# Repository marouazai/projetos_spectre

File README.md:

# projetos_spectre

1. Objectif du programme

Le programme réalise un analyseur de spectre audio temps réel sur la carte STM32F746G-DISCO.

Son rôle est de :

Capturer le son provenant du jack audio 3.5 mm.
Numériser ce son à 44,1 kHz.
Calculer sa Transformée de Fourier Rapide (FFT).
Afficher simultanément :
la forme d'onde du signal (oscilloscope)
le spectre fréquentiel (barres FFT colorées).

3. Logique générale du système

Le programme suit la chaîne de traitement suivante :

Signal Audio >>>Codec WM8994 >>> SAI2 >>> DMA >>> Buffer Audio >>> Prétraitement >>> FFT >>> Calcul des amplitudes>>> Affichage LCD

Le principe est :
  
1.Le matériel récupère le son.
2.Le DMA stocke les échantillons sans utiliser le CPU.
3.Le processeur analyse les données reçues.
4.Les résultats sont affichés en temps réel.

3. Taille de la FFT

Le programme utilise une FFT de 1024 points. À chaque traitement, un bloc de 1024 échantillons est analysé pour extraire son contenu fréquentiel. Ce choix représente un compromis entre la précision fréquentielle et la rapidité d'exécution. Avec une fréquence d'échantillonnage de 44,1 kHz, la résolution fréquentielle obtenue est d'environ 43 Hz par bin, ce qui permet de distinguer correctement les différentes composantes du signal audio.

4.Utilisation du DMA

Le transfert des données audio vers la mémoire est assuré par le contrôleur DMA (Direct Memory Access). Cette technique permet de transférer les échantillons directement depuis le périphérique audio vers la mémoire RAM sans solliciter le processeur. Ainsi, le microcontrôleur reste disponible pour effectuer les calculs FFT et l'affichage graphique, ce qui améliore considérablement les performances du système en temps réel.

5.Technique du Double Buffering

Afin d'éviter toute perte de données pendant l'acquisition audio, le programme utilise une technique appelée double buffering. Le buffer mémoire est divisé en deux parties. Pendant que le DMA remplit une moitié du buffer avec de nouvelles données audio, le processeur traite simultanément l'autre moitié. Cette méthode garantit une acquisition continue du signal tout en permettant son traitement en temps réel.

6.Gestion des interruptions DMA

Le DMA génère des interruptions lorsque la moitié ou la totalité du buffer est remplie. Ces interruptions ne réalisent aucun traitement complexe ; elles se contentent de positionner des indicateurs appelés flags. Cette approche permet de maintenir des interruptions très courtes et de réserver les calculs lourds, tels que la FFT et l'affichage graphique, à la boucle principale du programme. Cette organisation constitue une bonne pratique dans les systèmes embarqués temps réel.

7.Initialisation du système d'affichage

Lors du démarrage du programme, le module d'affichage LCD est initialisé afin de préparer l'écran pour l'affichage graphique. Le système configure les couleurs, les polices ainsi que les différentes zones d'affichage. Une zone supérieure est réservée à la représentation temporelle du signal tandis qu'une zone inférieure est utilisée pour afficher le spectre fréquentiel obtenu après calcul de la FFT.

8.Application de la fenêtre de Hanning

Avant d'effectuer la FFT, le programme applique une fenêtre de Hanning aux échantillons audio. Cette opération consiste à multiplier chaque échantillon par un coefficient calculé selon une fonction mathématique spécifique. L'objectif est de réduire les effets de bord liés à la découpe du signal en blocs, ce qui diminue les fuites spectrales et améliore la précision de l'analyse fréquentielle.

9.Calcul de la Transformée de Fourier Rapide

La FFT est réalisée grâce à la bibliothèque CMSIS-DSP optimisée pour les processeurs ARM Cortex-M7. Cette opération transforme le signal du domaine temporel vers le domaine fréquentiel. Le résultat permet de déterminer quelles fréquences sont présentes dans le signal ainsi que leur amplitude respective. Cette étape constitue le cœur du fonctionnement de l'analyseur de spectre.

10.Calcul des amplitudes fréquentielles

Après le calcul de la FFT, le programme détermine l'amplitude de chaque composante fréquentielle. Pour cela, il calcule le module des valeurs complexes obtenues à la sortie de la FFT. Ces amplitudes représentent l'énergie contenue dans chaque fréquence du signal audio et servent ensuite à construire l'affichage du spectre.

11.Conversion en décibels

Les amplitudes calculées sont converties en décibels à l'aide de la formule logarithmique 20·log10(x). Cette conversion permet d'obtenir une représentation plus proche de la perception humaine du son.

12.Affichage du spectre fréquentiel

La partie inférieure de l'écran affiche le spectre audio sous forme de 60 barres verticales. La hauteur de chaque barre est proportionnelle à l'amplitude de la bande fréquentielle correspondante. Les couleurs évoluent progressivement du vert vers le rouge, permettant d'identifier visuellement les différentes zones du spectre, des basses fréquences aux hautes fréquences.

13.Lissage de l'affichage

Afin d'améliorer le confort visuel, le programme applique un algorithme de lissage aux hauteurs des barres du spectre. Les barres montent rapidement lorsqu'une fréquence apparaît mais redescendent plus lentement lorsqu'elle disparaît.

14.Boucle principale du programme

La boucle principale assure la surveillance continue des indicateurs générés par le DMA. Lorsqu'une moitié du buffer est disponible, les données correspondantes sont immédiatement traitées par le module FFT puis affichées à l'écran. Grâce au double buffering, cette opération peut être réalisée en continu sans interrompre l'acquisition audio. Le système fonctionne ainsi en temps réel avec une faible charge processeur et sans perte d'échantillons.

Conclusion

L'architecture du programme repose sur une combinaison efficace entre acquisition audio, traitement numérique du signal et affichage graphique. L'utilisation du DMA, du double buffering et de la bibliothèque CMSIS-DSP permet de réaliser une analyse fréquentielle en temps réel tout en garantissant des performances élevées sur le microcontrôleur STM32F746G-DISCO. Le système offre ainsi une visualisation claire et instantanée des caractéristiques temporelles et fréquentielles du signal audio.

Réalisées par : Maroua Zaid , Chaimaa Es-saoudi .

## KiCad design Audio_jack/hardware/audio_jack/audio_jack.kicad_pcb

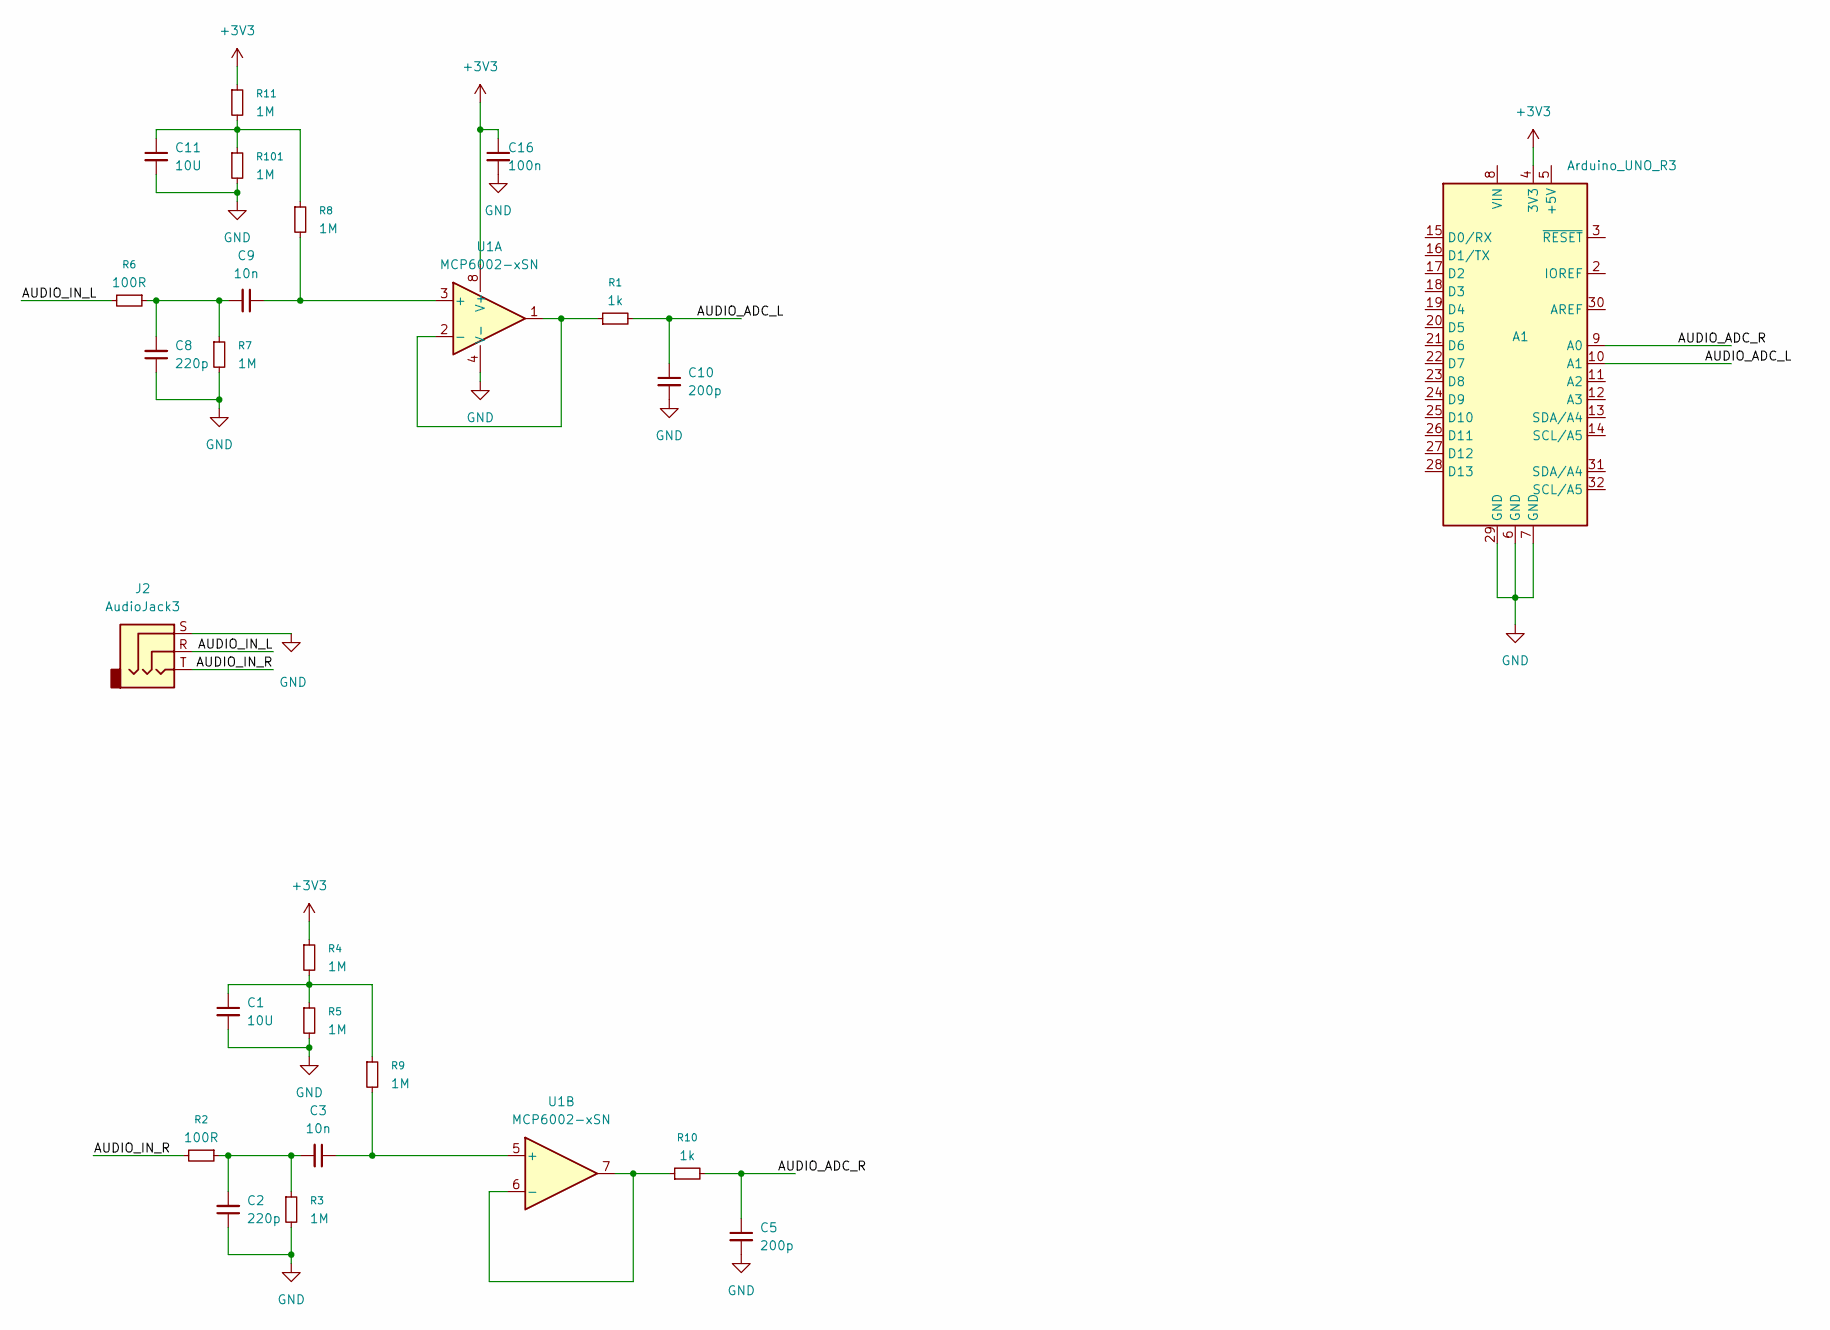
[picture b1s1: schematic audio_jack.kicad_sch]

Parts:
A1: Arduino_UNO_R3
C1, C11: 10U; C_0603_1608Metric
C2, C8: 220p; C_0603_1608Metric
C3, C9: 10n; C_0603_1608Metric
C5, C10: 200p; C_0603_1608Metric
C16: 100n; C_0603_1608Metric
J2: AudioJack3; Jack_3.5mm_CUI_SJ-3523-SMT_Horizontal
R1, R10: 1k; R_0603_1608Metric
R2, R6: 100R; R_0603_1608Metric
R3, R4, R5, R7, R8, R9, R11, R101: 1M; R_0603_1608Metric
U1: MCP6002-xSN; SOIC-8_3.9x4.9mm_P1.27mm

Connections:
+3V3: A1.4 (3V3), C16.1, R4.1, R11.1, U1.8 (V+); also elsewhere on the board
/AUDIO_ADC_L: A1.10 (A1), C10.1, R1.2
/AUDIO_ADC_R: A1.9 (A0), C5.1, R10.2
/AUDIO_IN_L: J2.R, R6.2
/AUDIO_IN_R: J2.T, R2.2
GND: A1.6 (GND), A1.7 (GND), A1.29 (GND), C1.2, C2.1, C5.2, C8.1, C10.2, C11.2, C16.2, J2.S, R3.2, R5.2, R7.2, R101.2, U1.4 (V-); also elsewhere on the board
unnamed: C1.1, R4.2, R5.1, R9.1
unnamed: C2.2, C3.2, R2.1, R3.1
unnamed: C8.2, C9.2, R6.1, R7.1
unnamed: C11.1, R8.1, R11.2, R101.1
unnamed: C9.1, R8.2, U1.3 (+)
unnamed: R1.1, U1.1, U1.2 (-)
unnamed: C3.1, R9.2, U1.5 (+)
unnamed: R10.1, U1.6 (-), U1.7

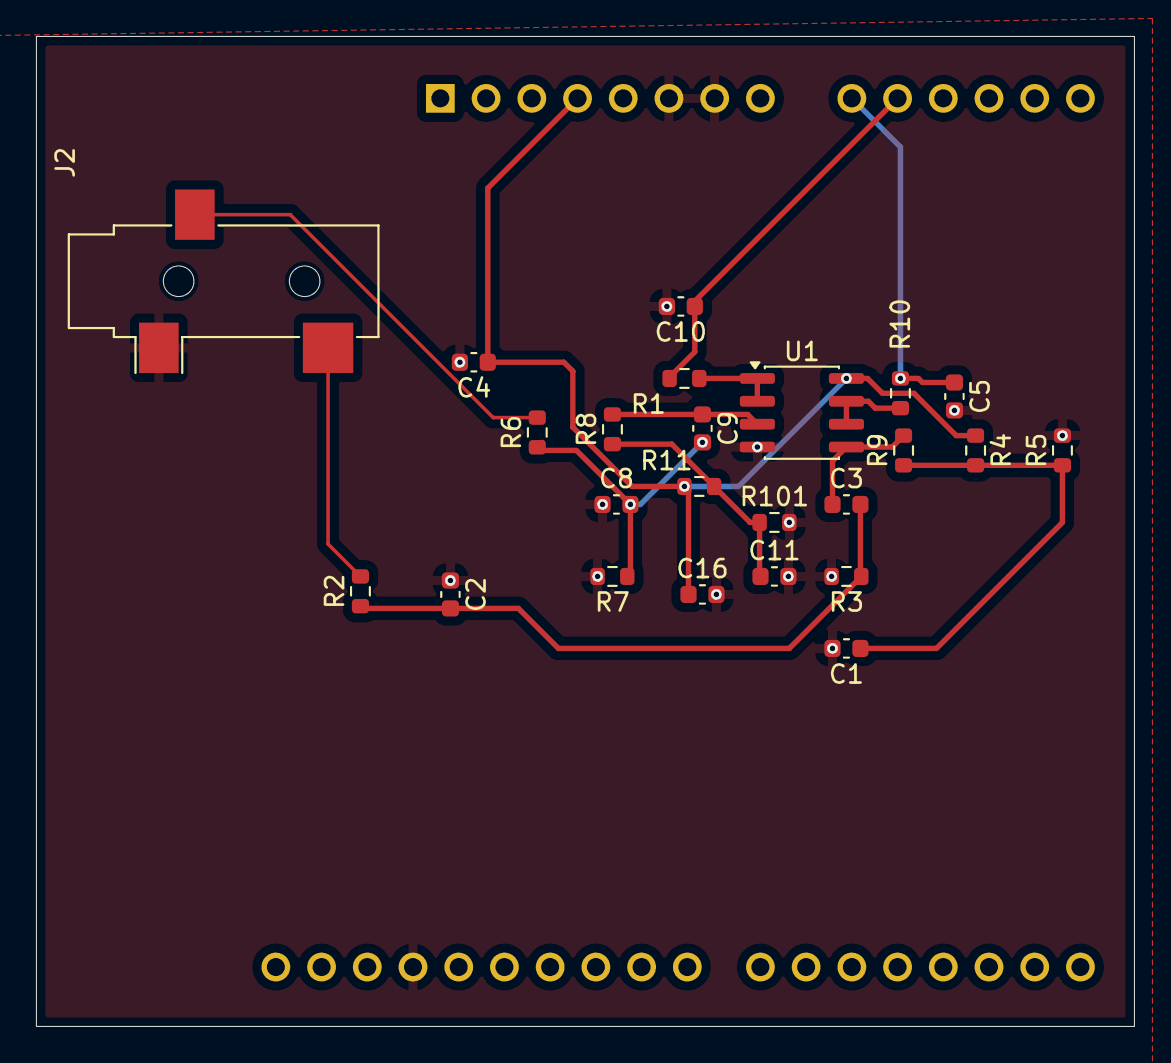
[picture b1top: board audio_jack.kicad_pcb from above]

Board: 2 copper layers, 61.0 x 55.0 mm, 25 parts (0 on the bottom side), 14 nets.

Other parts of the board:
C4: 100n; C_0603_1608Metric

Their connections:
+3V3: C4.1; also elsewhere on the board
GND: C4.2; also elsewhere on the board

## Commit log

2026-06-14 Ajout des dossiers AudioSpectrum1 et Audio_jack
2026-06-14 Convertir Audio_jack en dossier normal
2026-06-14 Expand README with program objectives and logic
    Added detailed program description and functionality overview.
